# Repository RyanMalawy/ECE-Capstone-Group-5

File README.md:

# Shoe Insole Pressure Sensor PCB
Schematic and Board Layout for Mizzou ECE Capstone Project

ESP 32 Code

## Repository Rules
When pushing KiCad files, do not push .lck files

## Toolchain
KiCad Version: 9.0

Arduino IDE

## Repository Structure
| Path                      | Description                     |
|---------------------------|---------------------------------|
| /Capstone-backups         | .zip backups                    |
| /Hierarchical Sheets      | .kicad_sch files                |
| /Spice                    | .kicad_sch files with Spice     |
| /Libs                     | Any imported IC models          |
| Capstone.kicad_sch        | Root schematic file             |
| Capstone.kicad_pro        | Project file                    |
| Capstone.kicad_pcb        | PCB file                        |

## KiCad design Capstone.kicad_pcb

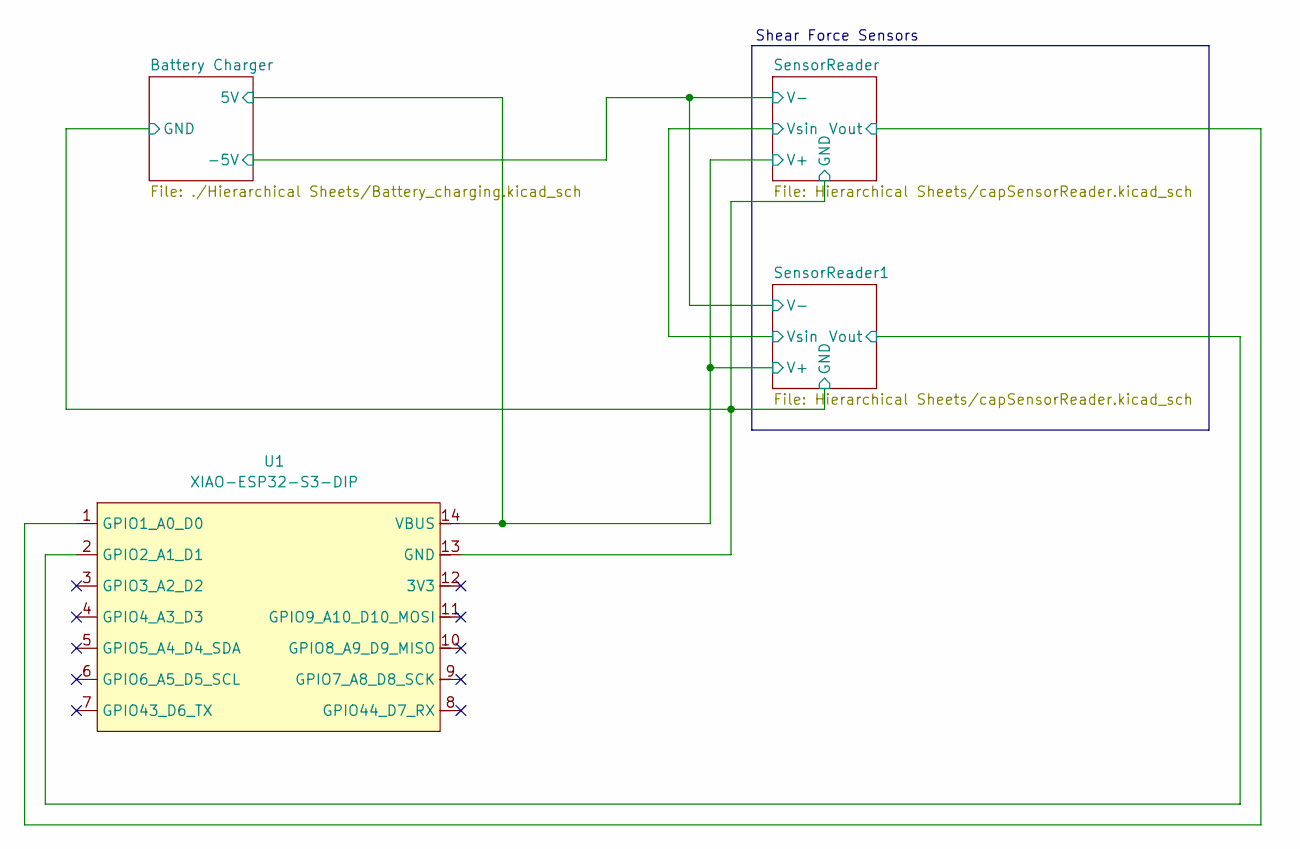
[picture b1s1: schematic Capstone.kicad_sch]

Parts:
U1: XIAO-ESP32-S3-DIP

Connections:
5V OUT: U1.14 (VBUS); also elsewhere on the board
/SensorReader1/Vout: U1.2 (GPIO2_A1_D1); also elsewhere on the board
/SensorReader/Vout: U1.1 (GPIO1_A0_D0); also elsewhere on the board
GND: U1.13 (GND); also elsewhere on the board

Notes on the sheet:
Shear Force Sensors

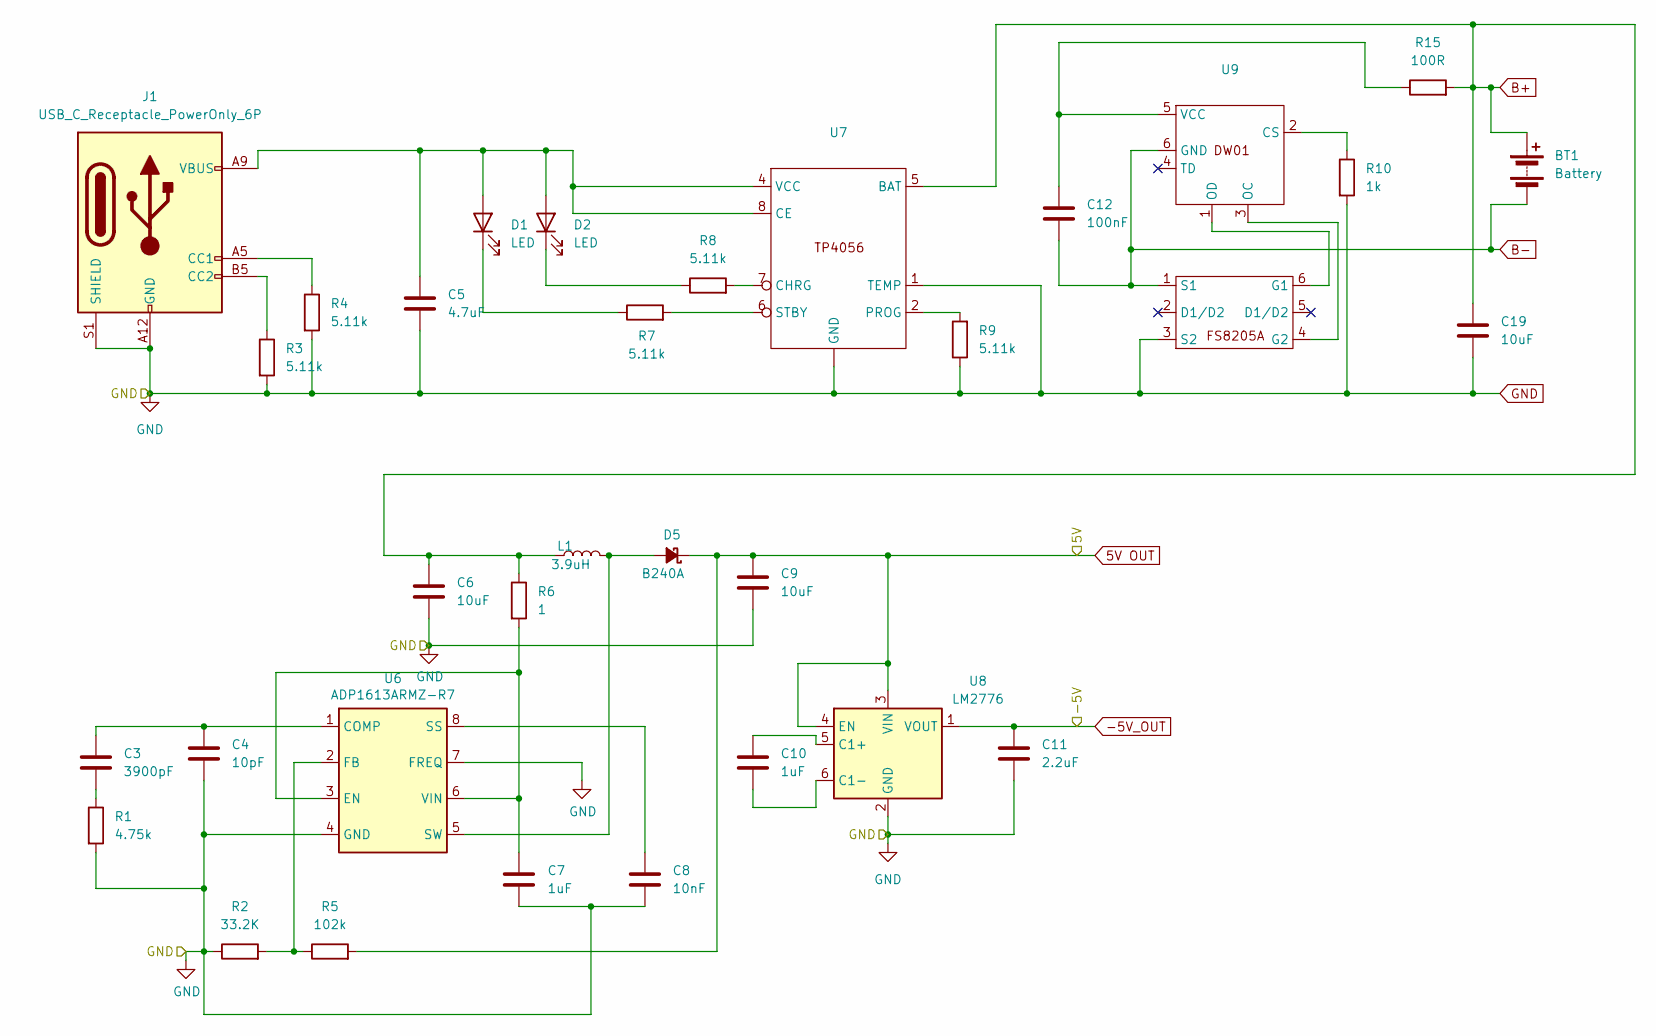
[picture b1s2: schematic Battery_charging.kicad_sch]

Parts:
BT1: Battery; JST_SUR_BM02B-SURS-TF_1x02-1MP_P0.80mm_Vertical
C3: 3900pF; C_Disc_D3.8mm_W2.6mm_P2.50mm
C4: 10pF; C_Disc_D3.8mm_W2.6mm_P2.50mm
C5: 4.7uF; C_Disc_D3.8mm_W2.6mm_P2.50mm
C6, C9, C19: 10uF; C_Disc_D3.8mm_W2.6mm_P2.50mm
C7, C10: 1uF; C_Disc_D3.8mm_W2.6mm_P2.50mm
C8: 10nF; C_Disc_D3.8mm_W2.6mm_P2.50mm
C11: 2.2uF; C_Disc_D3.8mm_W2.6mm_P2.50mm
C12: 100nF; C_Disc_D3.8mm_W2.6mm_P2.50mm
D1, D2: LED; LED_D3.0mm_Horizontal_O1.27mm_Z6.0mm
D5: B240A; D_SMA
J1: USB_C_Receptacle_PowerOnly_6P; USB_C_Receptacle_GCT_USB4135-GF-A_6P_TopMnt_Horizontal
L1: 3.9uH; L_Bourns-SRN4018
R1: 4.75k; R_Axial_DIN0204_L3.6mm_D1.6mm_P5.08mm_Horizontal
R2: 33.2K; R_Axial_DIN0204_L3.6mm_D1.6mm_P5.08mm_Horizontal
R3, R4, R7, R8, R9: 5.11k; R_Axial_DIN0204_L3.6mm_D1.6mm_P5.08mm_Horizontal
R5: 102k; R_Axial_DIN0204_L3.6mm_D1.6mm_P5.08mm_Horizontal
R6: 1; R_Axial_DIN0204_L3.6mm_D1.6mm_P5.08mm_Horizontal
R10: 1k; R_Axial_DIN0204_L3.6mm_D1.6mm_P5.08mm_Horizontal
R15: 100R; R_Axial_DIN0204_L3.6mm_D1.6mm_P5.08mm_Horizontal
U6: ADP1613ARMZ-R7; MSOP-8_3x3mm_P0.65mm
U7: SOT-23-8
U8: LM2776; SOT-23-6
U9, U10: SOT-23-6

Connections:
5V OUT: C9.1, D5.1 (K), R5.2, U8.3 (VIN), U8.4 (EN); also elsewhere on the board
-5V_OUT: C11.1, U8.1 (VOUT); also elsewhere on the board
B+: BT1.1 (+), C6.1, C19.1, L1.1, R6.1, R15.2, U7.5 (BAT)
B-: BT1.2 (-), C12.2, U9.6 (GND), U10.1 (S1)
GND: C4.2, C5.2, C6.2, C7.2, C8.2, C9.2, C11.2, C19.2, J1.A12 (GND), J1.B12 (GND), J1.S1 (SHIELD), R1.2, R2.1, R3.2, R4.2, R9.1, R10.2, U6.4 (GND), U6.7 (FREQ), U7. (GND), U7.1 (TEMP), U8.2 (GND), U10.3 (S2); also elsewhere on the board
unnamed: C3.2, R1.1
unnamed: C5.1, D1.2 (A), D2.2 (A), J1.A9 (VBUS), J1.B9 (VBUS), U7.4 (VCC), U7.8 (CE)
unnamed: D1.1 (K), R7.1
unnamed: D2.1 (K), R8.1
unnamed: D5.2 (A), L1.2, U6.5 (SW)
unnamed: J1.A5 (CC1), R4.1
unnamed: J1.B5 (CC2), R3.1
unnamed: C3.1, C4.1, U6.1 (COMP)
unnamed: C7.1, R6.2, U6.3 (EN), U6.6 (VIN)
unnamed: R2.2, R5.1, U6.2 (FB)
unnamed: C8.1, U6.8 (SS)
unnamed: R8.2, U7.7 (CHRG)
unnamed: R9.2, U7.2 (PROG)
unnamed: R7.2, U7.6 (STBY)
unnamed: C10.1, U8.5 (C1+)
unnamed: C10.2, U8.6 (C1-)
unnamed: R10.1, U9.2 (CS)
unnamed: C12.1, R15.1, U9.5 (VCC)
unnamed: U9.1 (OD), U10.6 (G1)
unnamed: U9.3 (OC), U10.4 (G2)

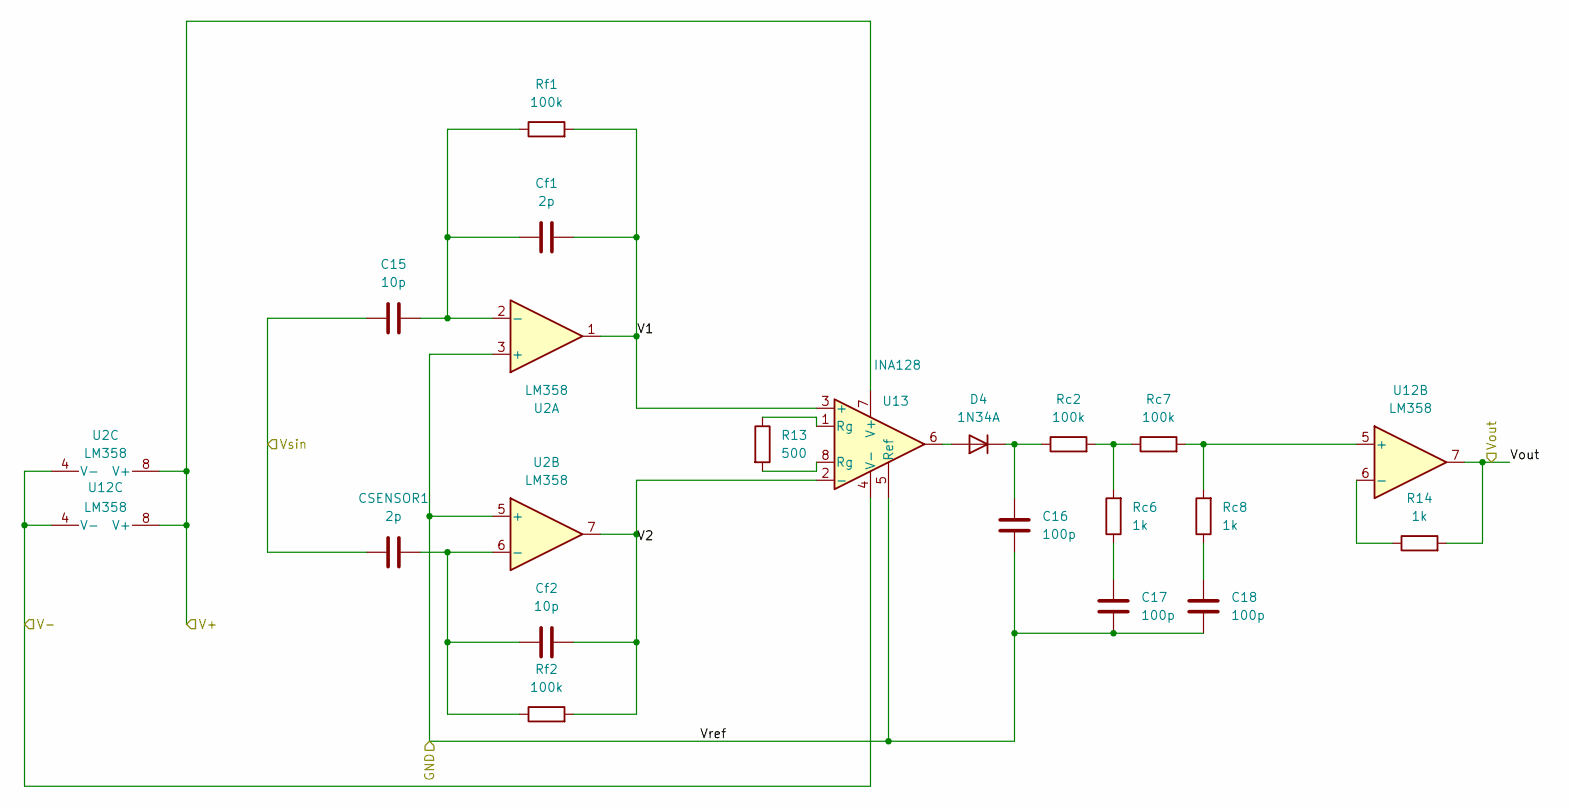
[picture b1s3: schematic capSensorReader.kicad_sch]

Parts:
C15: 10p
C16, C17, C18: 100p; C_Disc_D3.8mm_W2.6mm_P2.50mm
CSENSOR1: 2p
Cf1: 2p; C_Disc_D3.8mm_W2.6mm_P2.50mm
Cf2: 10p; C_Disc_D3.8mm_W2.6mm_P2.50mm
D4: 1N34A; D_DO-35_SOD27_P2.54mm_Vertical_AnodeUp
R13: 500; R_Axial_DIN0204_L3.6mm_D1.6mm_P5.08mm_Horizontal
R14: 1k; R_Axial_DIN0204_L3.6mm_D1.6mm_P5.08mm_Horizontal
Rc2, Rc7: 100k; R_Axial_DIN0204_L3.6mm_D1.6mm_P5.08mm_Horizontal
Rc6, Rc8: 1k; R_Axial_DIN0204_L3.6mm_D1.6mm_P5.08mm_Horizontal
Rf1, Rf2: 100k; R_Axial_DIN0204_L3.6mm_D1.6mm_P5.08mm_Horizontal
U2, U12: LM358; DIP-8_W7.62mm
U13: INA128; DIP-8_W7.62mm

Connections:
5V OUT: U2.8 (V+), U12.8 (V+), U13.7 (V+); also elsewhere on the board
-5V_OUT: U2.4 (V-), U12.4 (V-), U13.4 (V-); also elsewhere on the board
/SensorReader1/V1: Cf1.2, Rf1.2, U2.1, U13.3 (+)
/SensorReader1/V2: Cf2.2, Rf2.2, U2.7, U13.2 (-)
/SensorReader1/Vout: R14.2, U12.7; also elsewhere on the board
GND: C16.2, C17.2, C18.2, U2.3 (+), U2.5 (+), U13.5 (Ref); also elsewhere on the board
unnamed: C15.1, CSENSOR1.1
unnamed: C17.1, Rc6.1
unnamed: C18.1, Rc8.1
unnamed: D4.2 (A), U13.6
unnamed: C16.1, D4.1 (K), Rc2.1
unnamed: R13.1, U13.1 (Rg)
unnamed: R13.2, U13.8 (Rg)
unnamed: Rc2.2, Rc6.2, Rc7.1
unnamed: Cf1.1, Rf1.1, U2.2 (-)
unnamed: Cf2.1, Rf2.1, U2.6 (-)
unnamed: Rc7.2, Rc8.2, U12.5 (+)
unnamed: R14.1, U12.6 (-)

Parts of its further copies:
C1, C13, C14: 100p; C_Disc_D3.8mm_W2.6mm_P2.50mm
Cf3: 2p; C_Disc_D3.8mm_W2.6mm_P2.50mm
Cf4: 10p; C_Disc_D3.8mm_W2.6mm_P2.50mm
D3: 1N34A; D_DO-35_SOD27_P2.54mm_Vertical_AnodeUp
R11: 1k; R_Axial_DIN0204_L3.6mm_D1.6mm_P5.08mm_Horizontal
R12: 500; R_Axial_DIN0204_L3.6mm_D1.6mm_P5.08mm_Horizontal
Rc1, Rc4: 100k; R_Axial_DIN0204_L3.6mm_D1.6mm_P5.08mm_Horizontal
Rc3, Rc5: 1k; R_Axial_DIN0204_L3.6mm_D1.6mm_P5.08mm_Horizontal
Rf3, Rf4: 100k; R_Axial_DIN0204_L3.6mm_D1.6mm_P5.08mm_Horizontal
U3: INA128; DIP-8_W7.62mm
U4, U5: LM358; DIP-8_W7.62mm

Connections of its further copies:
5V OUT: U3.7 (V+), U4.8 (V+), U5.8 (V+); also elsewhere on the board
-5V_OUT: U3.4 (V-), U4.4 (V-), U5.4 (V-); also elsewhere on the board
/SensorReader/V1: Cf3.2, Rf3.2, U3.3 (+), U4.1
/SensorReader/V2: Cf4.2, Rf4.2, U3.2 (-), U4.7
/SensorReader/Vout: R11.2, U5.7; also elsewhere on the board
GND: C1.2, C13.2, C14.2, U3.5 (Ref), U4.3 (+), U4.5 (+); also elsewhere on the board
unnamed: C13.1, Rc3.1
unnamed: C14.1, Rc5.1
unnamed: D3.2 (A), U3.6
unnamed: C1.1, D3.1 (K), Rc1.1
unnamed: R12.1, U3.1 (Rg)
unnamed: R12.2, U3.8 (Rg)
unnamed: Rc1.2, Rc3.2, Rc4.1
unnamed: Cf3.1, Rf3.1, U4.2 (-)
unnamed: Cf4.1, Rf4.1, U4.6 (-)
unnamed: Rc4.2, Rc5.2, U5.5 (+)
unnamed: R11.1, U5.6 (-)

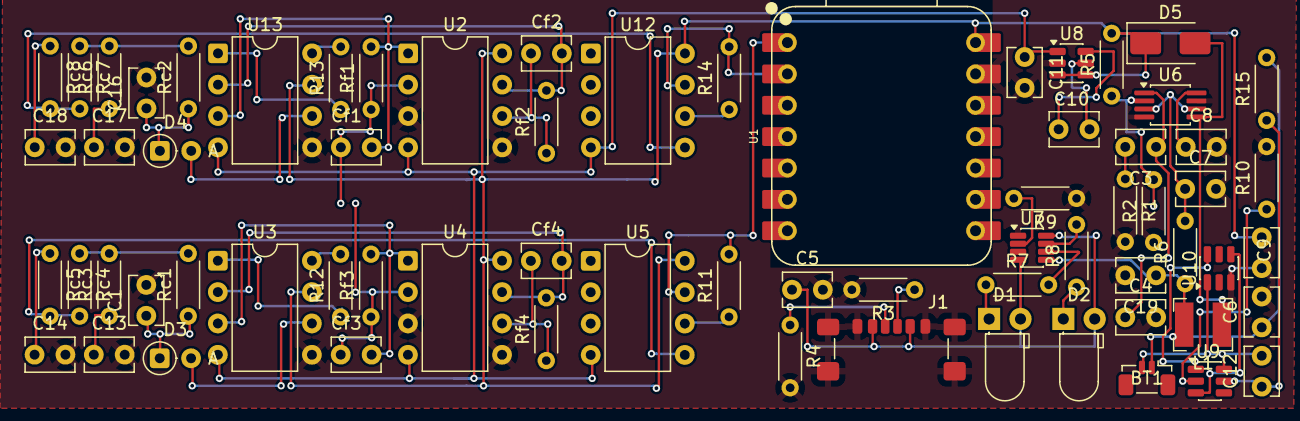
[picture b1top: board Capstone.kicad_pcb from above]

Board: 2 copper layers, 68 parts (0 on the bottom side), 53 nets.

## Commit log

2026-02-02 File upload
2026-02-03 File organizing
2026-02-03 Remove Locks
2026-02-03 Created Folders for Libs and Spice files
    has temp .txt files to show the folders before actual files are added
2026-02-06 Added Binary counting IC
    IC converts clock pulse from ESP 32 into 3 bit binary for MUX
    74HC161 ECAD files added to \Libs
2026-02-06 SN74HC161DR symbol update
2026-02-06 Cleanup
2026-02-06 create .gitignore
    added .lck files to .gitignore
2026-02-06 Added Project Component Libary
    CapstoneComps libary for project specific components
    also added Capstone.kicad_prl to .gitignore
2026-02-06 Added New Libraries
    ESP32 Library - Footprint & Schematics
    Binary Counter Footrprint Added
2026-02-06 Update .gitignore update PCB footprints
2026-02-06 added .gitignore fp-info-cache
2026-02-06 Update Root
    Working on simulations
2026-02-07 layout of amplifier 1 - begin
2026-02-08 Continued researching IA topologies and design strategies -- updated amplifier schematics with 2 Op Amp topology
2026-02-08 Cited a source for the instr amp topology
2026-02-09 Contined looking into topologies and general op amp information - added notes to amplifier schematics.
2026-02-09 remove Hierarchical Sheets folder inside Hierarchical Sheets foler
2026-02-09 Binary Update
2026-02-09 Binary Cleanup
2026-02-09 Switched to pre-made instr. amp. - made preliminary choice of IA
2026-02-09 changed the description on the buffer op amp in amplifier schematic
2026-02-09 Binary Counter LTSpice
2026-02-09 remove autosave
2026-02-10 Added new INA350CDS to part library and placed it into the schematic
2026-02-11 LTSpice Update
2026-02-11 LTSpice save
2026-02-12 Added 2nd order low-pass filter topology - Still working on exact design
2026-02-13 added battery charger
2026-02-13 Link Battery Charger
2026-03-09 Sensor Reading Circuit
2026-03-09 Redo Base Project file add code
2026-03-12 Added rectifier and passive low-pass filter (RC)
2026-03-13 Better Sensor Reader
2026-03-16 Update Main Sub Sheets
2026-03-16 Main Update
2026-03-16 Battery Charging Moved
2026-03-16 PCB designed rev1.0
2026-03-19 Remove Ground fill around ESP 32
2026-03-31 Added ocsillator + logic circuit (in-progress)
2026-03-31 continued work on osc/logic circuit
2026-04-01 timer oscillator
2026-04-01 timer oscillator circuit
2026-04-01 Remove extra ref sensor
    each module had a reference sensor before, now have single ref sensor comparing to both sensors
2026-04-13 Revert "Remove extra ref sensor"
    This reverts commit 7f0b0207ac24b991faee57c630f393e10dd69dda.
